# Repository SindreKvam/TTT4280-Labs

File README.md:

# README

To pull submodules run the following command
```
git pull --recurse-submodules
```

## pigpio installation
```
cd pigpio
make
sudo make install
```

## picamera2 installation
```
sudo apt install -y python3-picamera2
pip3 install picamera2
```

## adc_sampler

To compile, run the following commands:
```
cd src
make
```

Usage is as following:
```
sudo adc_sampler <sample-count> [output]
```

## Run RPyC server
The RPyC server is required to be ran by root to allow using DMAs.

First we need to install python packages on root level:
```
sudo apt install python3-numpy
sudo python3 -m pip install rpyc --break-system-packages
```

Then we can run the server
```
sudo python3 src/server/server.py
```

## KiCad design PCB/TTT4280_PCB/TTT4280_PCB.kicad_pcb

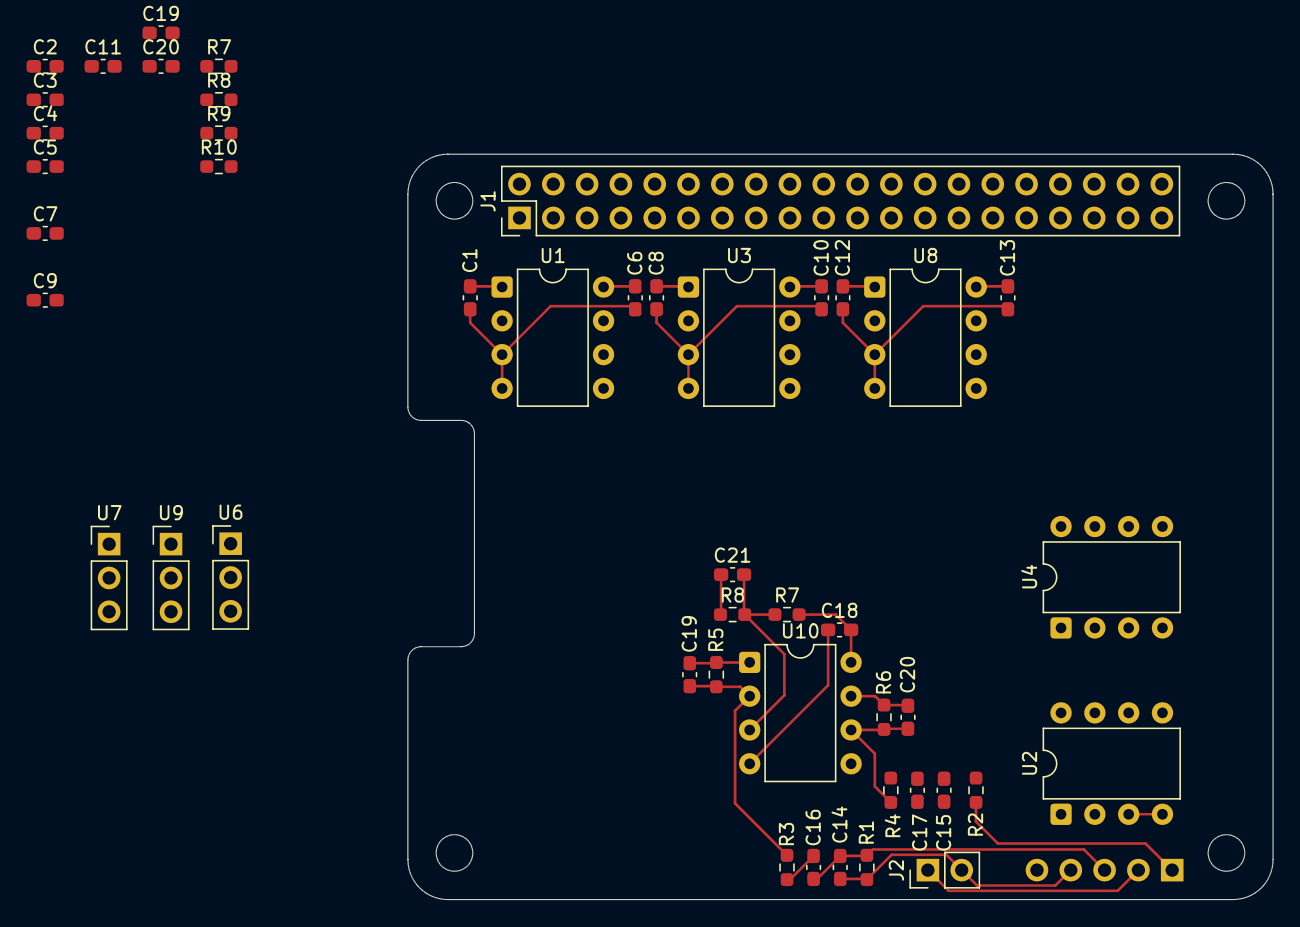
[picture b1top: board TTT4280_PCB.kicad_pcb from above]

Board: 2 copper layers, 65.0 x 56.0 mm, 47 parts (1 on the bottom side), 24 nets.

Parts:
C1, C2, C6, C7, C8, C9, C10, C11, C12, C13: 1uF; C_0603_1608Metric_Pad1.08x0.95mm_HandSolder
C3, C4: 100uF; C_0603_1608Metric_Pad1.08x0.95mm_HandSolder
C5, C18, C19, C20#2, C21: 100nF; C_0603_1608Metric_Pad1.08x0.95mm_HandSolder
C14, C15: 1nF; C_0603_1608Metric_Pad1.08x0.95mm_HandSolder
C16, C17: 45.5uF; C_0603_1608Metric_Pad1.08x0.95mm_HandSolder
C19#2, C20: 5.7nF; C_0603_1608Metric_Pad1.08x0.95mm_HandSolder
J1: Raspberry_Pi_2_3; PinHeader_2x20_P2.54mm_Vertical
J2: Conn_01x02_Pin; PinHeader_1x02_P2.54mm_Vertical
R1, R2, R3, R4: 1k; R_0603_1608Metric_Pad0.98x0.95mm_HandSolder
R5, R6, R7, R7#2, R8, R8#2, R9, R10: 10k; R_0603_1608Metric_Pad0.98x0.95mm_HandSolder
U1, U2, U3, U4, U8: MCP3201; DIP-8_W7.62mm
U5: K-LC6; PinSocket_1x05_P2.54mm_Horizontal
U6, U7, U9: MAX4466; PinHeader_1x03_P2.54mm_Vertical
U10: MCP6002-xMC; DIP-8_W7.62mm

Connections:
+1V65: C21.2, R7#2.1, R8.2, U10.3 (+), U10.5 (+)
+3V3: C1.1, C2.1, C3.1, C4.1, C5.2, C6.1, C7.1, C8.1, C9.1, C10.1, C11.1, C12.1, C13.1, C18.2, J1.1 (3V3), J1.17 (3V3), R7.2, R7#2.2, R9.2, U1.1 (Vref), U1.8 (Vdd), U2.1 (Vref), U2.8 (Vdd), U3.1 (Vref), U3.8 (Vdd), U4.1 (Vref), U4.8 (Vdd), U6.3 (VCC), U7.3 (VCC), U8.1 (Vref), U8.8 (Vdd), U9.3 (VCC), U10.8 (V+)
+5V: J2.1, U5.2 (VCC)
/CLK: J1.23 (SCLK0/GPIO11), U1.7 (CLK), U2.7 (CLK), U3.7 (CLK), U4.7 (CLK), U8.7 (CLK)
/DATA1: J1.16 (GPIO23), U1.6 (Dout)
/DATA2: J1.18 (GPIO24), U3.6 (Dout)
/DATA3: J1.22 (GPIO25), U8.6 (Dout)
/DATA4: J1.37 (GPIO26), U2.6 (Dout)
/DATA5: J1.13 (GPIO27), U4.6 (Dout)
/IF_I: C14.1, C16.1, R1.1, U5.3 (IF_I)
/IF_Q: C15.1, C17.1, R2.1, U5.1 (IF_Q)
/MIC1: U1.2 (IN+), U6.1 (OUT)
/MIC2: U3.2 (IN+), U7.1 (OUT)
/MIC3: U8.2 (IN+), U9.1 (OUT)
/filtered_I: C19#2.2, R5.2, U2.2 (IN+), U10.1
/filtered_Q: C20.2, R6.2, U4.2 (IN+), U10.7
/~CS: J1.24 (~CE0/GPIO8), U1.5 (~CS/SHDN), U2.5 (~CS/SHDN), U3.5 (~CS/SHDN), U4.5 (~CS/SHDN), U8.5 (~CS/SHDN)
GND: C1.2, C2.2, C3.2, C4.2, C5.1, C6.2, C7.2, C8.2, C9.2, C10.2, C11.2, C12.2, C13.2, C14.2, C15.2, C18.1, C19.1, C20#2.1, C21.1, J1.6 (GND), J1.9 (GND), J1.14 (GND), J1.20 (GND), J1.25 (GND), J1.30 (GND), J1.34 (GND), J1.39 (GND), J2.2, R1.2, R2.2, R8.1, R8#2.1, R10.1, U1.3 (IN-), U1.4 (Vss), U2.3 (IN-), U2.4 (Vss), U3.3 (IN-), U3.4 (Vss), U4.3 (IN-), U4.4 (Vss), U5.4 (GND), U6.2 (GND), U7.2 (GND), U8.3 (IN-), U8.4 (Vss), U9.2 (GND), U10.4 (V-)
unnamed: C16.2, R3.1
unnamed: C17.2, R4.1
unnamed: C19.2, R7.1, R8#2.2
unnamed: C19#2.1, R3.2, R5.1, U10.2 (-)
unnamed: C20#2.2, R9.1, R10.2
unnamed: C20.1, R4.2, R6.1, U10.6 (-)

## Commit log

2025-01-23 Add provided ADC sampler code
2025-01-23 Added pigpio submodule
2025-01-23 Added README
2025-01-23 Created makefile to compile adc_sampler
2025-01-23 Updated pins to match setup
2025-01-23 Always recompile adc_sampler when running make
2025-01-23 Added provided script to parse data from ADC
2025-01-23 Minor bug fix
2025-01-23 Print output, and do not push output data to git
2025-01-23 Inital server and client
2025-01-23 updated gitignore
2025-01-23 formatting change
2025-01-23 Added easy function to check if communication works
2025-01-23 Improved relative path handling
2025-01-23 Fixed call arguments
2025-01-23 Managed to successfully read data from rpi
2025-01-23 Added information on how to run python server
2025-01-23 Allow pickling
2025-01-23 Successfully read and plot data
2025-01-23 Add plots
2025-01-24 Removed magical numbers and moved functionality to own method
2025-01-24 Swapped matplotlib backend to Tkinter
2025-01-24 Added dc_block functionality
2025-01-24 Added output data folder to contain data measured
2025-01-24 Updated number of samples to read
2025-01-24 Ignore .npz files from numpy
2025-01-24 Client overhaul, client only saves to file, cli to plot and analyse data
2025-01-28 Moved most functionality to a function
2025-01-28 Fixed adc value to voltage level function
2025-01-28 Fixed folder
2025-02-05 Added option to listen to signal
2025-02-05 Added commandline arguments to client.py
2025-02-05 Plot signal to noise ratio after doing a network measurement
2025-02-10 Updated function to plot fft channels
2025-02-10 Added calculate snr from psd!
2025-02-18 Uploaded jupyter notbook folder for Lab 1 (lab 2)
2025-02-18 Moved notebook into own folder
2025-02-19 Initial revision of acoustic lab find angle in "real time"
2025-02-20 Calculate running mean and std
2025-02-20 removed invalid minus sign
2025-02-20 Use arctan2 instead of adding pi to result
2025-02-20 formalia changes
2025-02-20 Minus sign was not unnecessary
2025-03-03 Added notebook for optics lab
2025-03-03 Added part 2 of pre-work
2025-03-05 Added provided record_video.py file
2025-03-06 Renamed lab 2 to acoustic lab
2025-03-06 Added radar lab notebook
2025-03-06 Replaced provided record video file with rpyc server
2025-03-06 Start servers in threads
2025-03-06 Updated initialization of the camera
2025-03-06 Attempt expose files
2025-03-06 made aws_gain adjustable
2025-03-07 Added contrast measurement
2025-03-07 pylint fixes
2025-03-07 removed acoustic lab cli
2025-03-07 Updated readme and gitignore
2025-03-07 Fixed encoding on server
2025-03-07 Added files for running optics measurements, and for analysing optics data
2025-03-07 Added alternative plotting method for fft related to acoustic lab
2025-03-07 Added vscode settings for better linting
2025-03-13 Initial revision of KiCad project, imported from Altium
2025-03-13 Added microphones
2025-03-19 Added simulations of active filter for radar lab
2025-03-19 Added radar lab files
2025-03-19 Added plt file for LTspice simulations
2025-03-19 Deleted output data folder
2025-03-19 Made updates to PCB, schematic done.
2025-03-19 Updated module docstring
2025-04-25 Updated some text to norwegian, added option to measure transmittance
